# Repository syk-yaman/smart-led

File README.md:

# Smart LED

An AVR board to control home lighting autonomously. It provides automatic control of LED lighting (12vdc) according to:

* Time schedule: active during daily work time except for holidays.
* People movement: turning on lighting automatically when sensing movement using a PIR extension.
* Electric supply status: provides auxiliary lighting when needed (in case of a power outage).
* Illumination level sensing: no need to turn on the lighting when there is enough lighting.

Also providing manual control:

- Directly using onboard buttons.
- Remotely using an infrared remote control (RC5 based).

# Specifications

**Inputs:**

- 12v DC power supply.
- 220v AC (power detection).

**Output:**

- 12v DC power supply for LEDs.

**Schematic**:

**Main parts:**

- ATmega 8A
- DS1307 RTC
- PIR module ([link](https://www.adafruit.com/product/189))
- 5v DC Relay
- Infrared receiver

See [BOM](https://raw.githubusercontent.com/syk-yaman/smart-led/master/PCB/BOM.txt) for further details.

# Development

Required tools:

* Atmel Studio
* Autodesk Eagle
* A brain

**BE AWARE OF ELECTRIC SHOCK, 220V POWER SUPPLY SHOULD BE TAKEN SERIOUSLY. PLEASE TAKE SAFETY MEASURES FIRST**

## License

###### The software side is licensed under MIT License

```
MIT License

Copyright (c) [year] [fullname]

Permission is hereby granted, free of charge, to any person obtaining a copy
of this software and associated documentation files (the "Software"), to deal
in the Software without restriction, including without limitation the rights
to use, copy, modify, merge, publish, distribute, sublicense, and/or sell
copies of the Software, and to permit persons to whom the Software is
furnished to do so, subject to the following conditions:

The above copyright notice and this permission notice shall be included in all
copies or substantial portions of the Software.

THE SOFTWARE IS PROVIDED "AS IS", WITHOUT WARRANTY OF ANY KIND, EXPRESS OR
IMPLIED, INCLUDING BUT NOT LIMITED TO THE WARRANTIES OF MERCHANTABILITY,
FITNESS FOR A PARTICULAR PURPOSE AND NONINFRINGEMENT. IN NO EVENT SHALL THE
AUTHORS OR COPYRIGHT HOLDERS BE LIABLE FOR ANY CLAIM, DAMAGES OR OTHER
LIABILITY, WHETHER IN AN ACTION OF CONTRACT, TORT OR OTHERWISE, ARISING FROM,
OUT OF OR IN CONNECTION WITH THE SOFTWARE OR THE USE OR OTHER DEALINGS IN THE
SOFTWARE.
```

###### The hardware side is licensed under CERN License

```
This documentation describes Open Hardware and is licensed under the CERN OHL v. 1.2.

You may redistribute and modify this documentation under the terms of the CERN OHL v.1.2. (http://ohwr.org/cernohl). This documentation is distributed WITHOUT ANY EXPRESS OR IMPLIED WARRANTY, INCLUDING OF MERCHANTABILITY, SATISFACTORY QUALITY AND FITNESS FOR A PARTICULAR PURPOSE. Please see the CERN OHL v.1.2 for applicable conditions
```

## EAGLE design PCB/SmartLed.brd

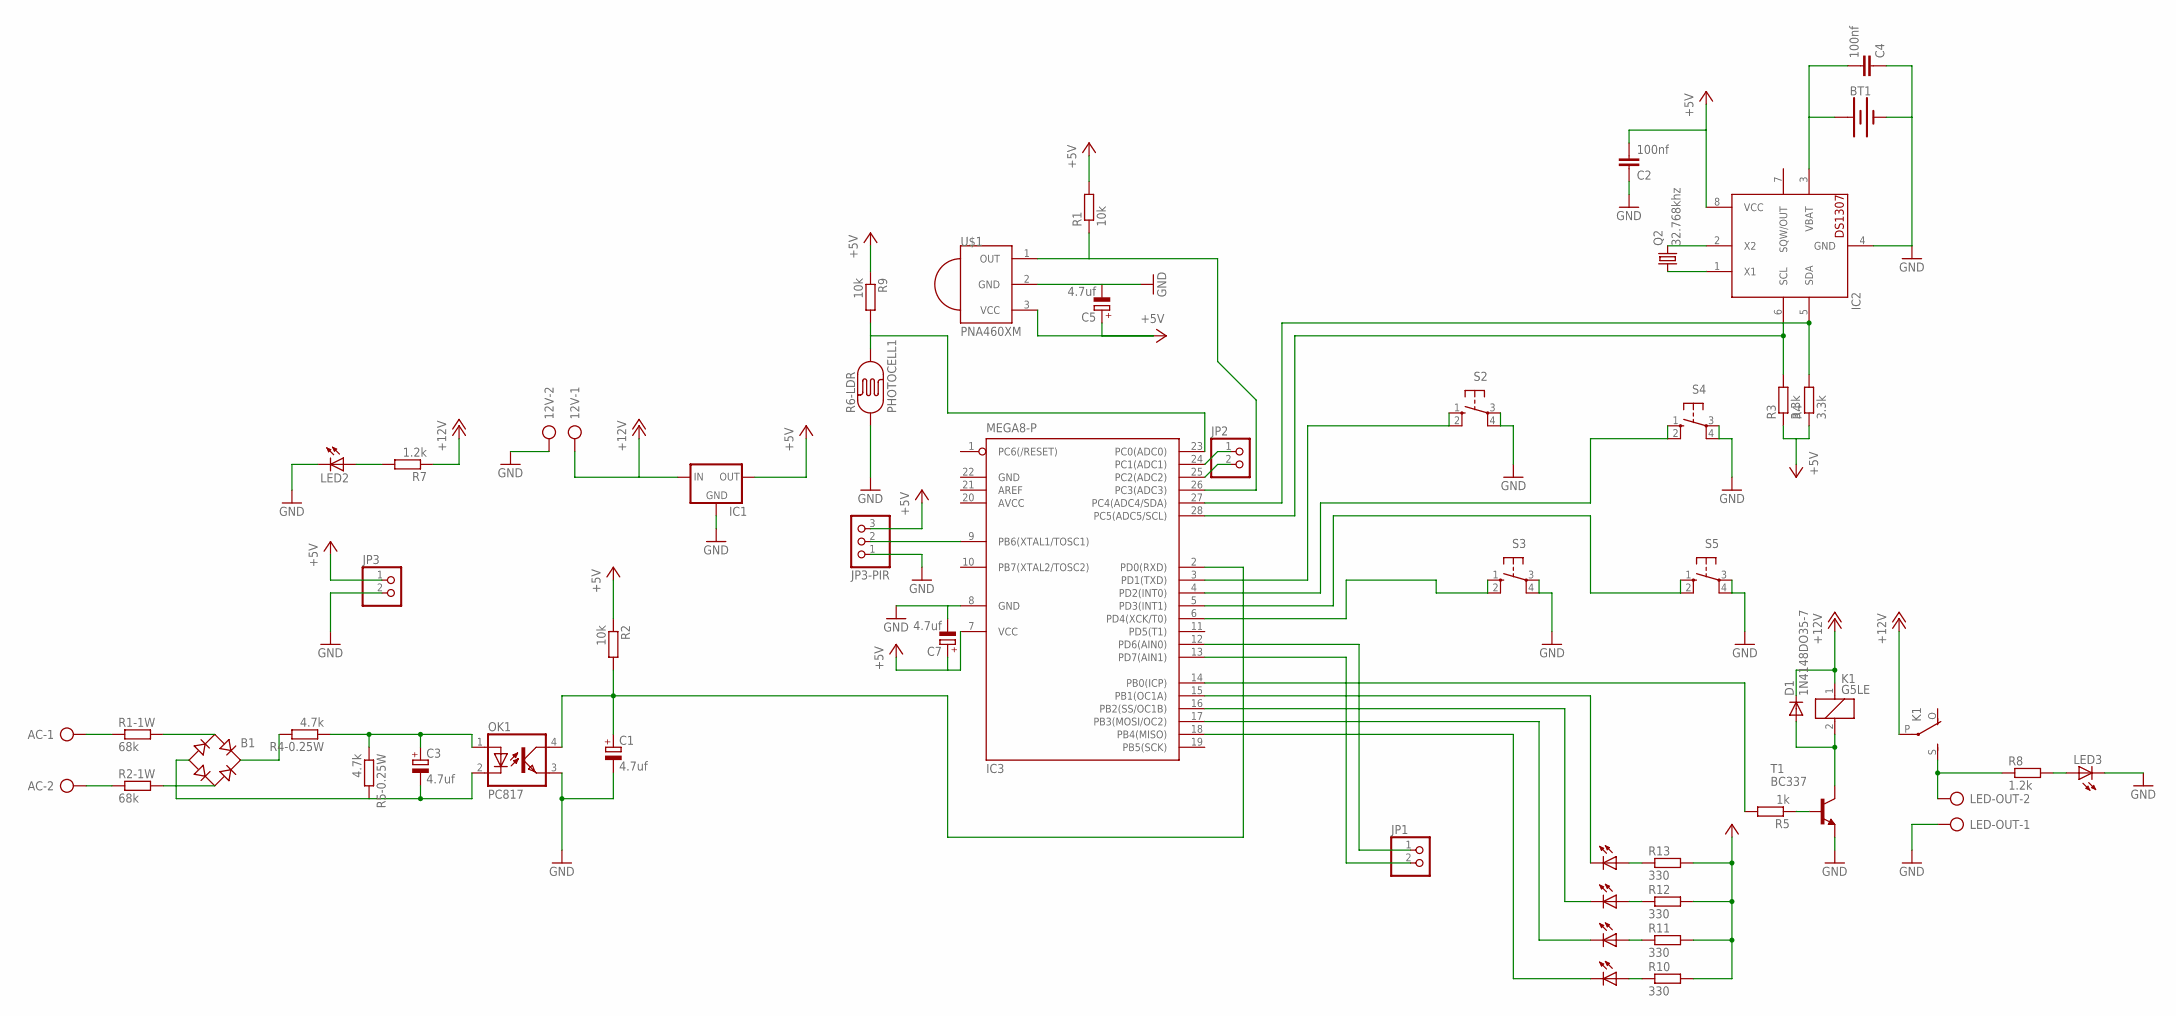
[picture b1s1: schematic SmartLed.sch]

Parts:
12V: AK500/2
AC: AK500/2
B1: RB1A
BT1: BATTERY-20MM_PTH; BATTCOM_20MM_PTH
C1, C3, C5, C7: 4.7uf; E2,5-5
C2, C4: 100nf; C025-025X050
D1: 1N4148DO35-7; DO35-7
IC1: 78XXL
IC2: DS1307; DIL08
IC3: MEGA8-P; DIL28-3
JP1, JP2, JP3: PINHD-1X2; 1X02
JP3-PIR: PINHD-1X3; 1X03
K1: G5LE
LED2, LED3, LED5, LED6, LED7, LED8: LED3MM
LED-OUT: AK500/2
OK1: PC817; DIL04
Q2: 32.768khz; TC26V
R1, R2, R9: 10k; 0207/10
R1-1W, R2-1W: 68k; 0411/15
R3, R4: 3.3k; 0207/10
R4-0.25W, R5-0.25W: 4.7k; 0207/10
R5: 1k; 0207/10
R6-LDR: PHOTOCELL1; LDR_OFFBOARD
R7, R8: 1.2k; 0207/10
R10, R11, R12, R13: 330; 0207/10
S2, S3, S4, S5: 10-XX; B3F-10XX
T1: BC337; TO92
U$1: PNA460XM

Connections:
+5V: C2.2, C5.+, C7.+, IC1.OUT, IC2.8 (VCC), IC3.7 (VCC), JP3.1, JP3-PIR.3, R1.2, R2.1, R3.1, R4.1, R9.1, R10.2, R11.2, R12.2, R13.2, U$1.3 (VCC)
+12V: 12V.1, D1.C, IC1.IN, K1.1, K1.P, R7.1
AVCC: IC3.20 (AVCC)
GND: 12V.2, BT1.2 (-), C1.-, C2.1, C4.1, C5.-, C7.-, IC1.GND, IC2.4 (GND), IC3.8 (GND), IC3.22 (GND), JP3.2, JP3-PIR.1, LED2.K (C), LED3.K (C), LED-OUT.1, OK1.3 (EMIT), R6-LDR.1, S2.3, S2.4 (P1), S3.3, S3.4 (P1), S4.3, S4.4 (P1), S5.3, S5.4 (P1), T1.1 (E), U$1.2 (GND)
unnamed: AC.1, R1-1W.1
unnamed: AC.2, R2-1W.1
unnamed: B1.AC1, R1-1W.2
unnamed: B1.AC2, R2-1W.2
unnamed: B1.+, R4-0.25W.2
unnamed: C3.+, OK1.1 (A), R4-0.25W.1, R5-0.25W.1
unnamed: B1.-, C3.-, OK1.2 (C), R5-0.25W.2
unnamed: K1.S, LED-OUT.2, R8.1
unnamed: R5.1, T1.2 (B)
unnamed: IC3.14 (PB0(ICP)), R5.2
unnamed: C1.+, IC3.2 (PD0(RXD)), OK1.4 (COL), R2.2
unnamed: IC2.6 (SCL), IC3.28 (PC5(ADC5/SCL)), R3.2
unnamed: IC2.5 (SDA), IC3.27 (PC4(ADC4/SDA)), R4.2
unnamed: D1.A, K1.2, T1.3 (C)
unnamed: LED2.A, R7.2
unnamed: LED3.A, R8.2
unnamed: IC3.15 (PB1(OC1A)), LED8.K (C)
unnamed: LED8.A, R13.1
unnamed: IC3.9 (PB6(XTAL1/TOSC1)), JP3-PIR.2
unnamed: IC3.16 (PB2(SS/OC1B)), LED7.K (C)
unnamed: IC2.1 (X1), Q2.1
unnamed: IC2.2 (X2), Q2.2
unnamed: LED7.A, R12.1
unnamed: IC3.17 (PB3(MOSI/OC2)), LED6.K (C)
unnamed: LED6.A, R11.1
unnamed: IC3.18 (PB4(MISO)), LED5.K (C)
unnamed: LED5.A, R10.1
unnamed: IC3.3 (PD1(TXD)), S2.1 (S), S2.2 (S1)
unnamed: IC3.24 (PC1(ADC1)), JP2.1
unnamed: IC3.6 (PD4(XCK/T0)), S3.1 (S), S3.2 (S1)
unnamed: IC3.4 (PD2(INT0)), S4.1 (S), S4.2 (S1)
unnamed: IC3.5 (PD3(INT1)), S5.1 (S), S5.2 (S1)
unnamed: IC3.25 (PC2(ADC2)), JP2.2
unnamed: IC3.23 (PC0(ADC0)), R6-LDR.2, R9.2
unnamed: IC3.12 (PD6(AIN0)), JP1.1
unnamed: IC3.13 (PD7(AIN1)), JP1.2
unnamed: BT1.1 (+), C4.2, IC2.3 (VBAT)
unnamed: IC3.26 (PC3(ADC3)), R1.1, U$1.1 (OUT)

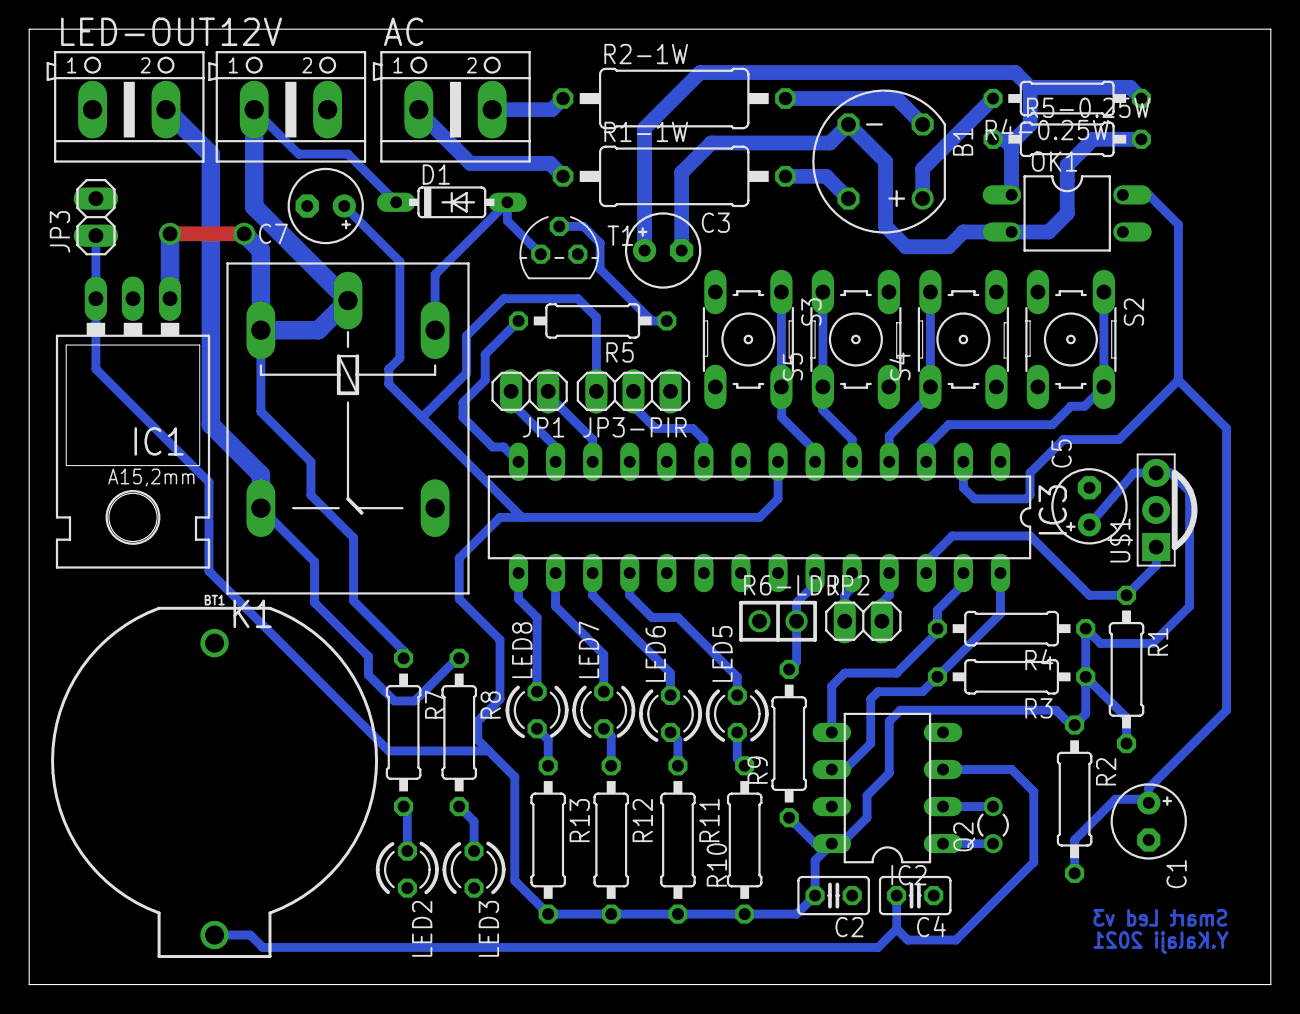
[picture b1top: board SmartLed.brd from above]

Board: 2 copper layers, 85.1 x 65.5 mm, 51 parts (0 on the bottom side), 41 nets.

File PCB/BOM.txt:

Partlist exported from C:/Users/Yaman-PC/projects/smart-led/PCB/SmartLed.sch at 12-Jun-18 10:46 PM

Qty Value        Device           Package          Parts                              Description                          MF MPN          OC_FARNELL OC_NEWARK PROD_ID    SF_SKU   
4                10-XX            B3F-10XX         S2, S3, S4, S5                     OMRON SWITCH                            B3F-1000     176432     36M3542                       
1                79XXL            79XXL            IC1                                VOLTAGE REGULATOR                                                                             
3                AK500/2          AK500/2          12V, AC, LED-OUT                   CONNECTOR                                            unknown    unknown                       
1                BATTERY-20MM_PTH BATTCOM_20MM_PTH BT1                                Battery - Single Cell                                                     BATT-09031 PRT-00783
6                LED3MM           LED3MM           LED2, LED3, LED5, LED6, LED7, LED8 LED                                                                                           
2                PINHD-1X2        1X02             JP1, JP3                           PIN HEADER                                                                                    
1                PINHD-1X3        1X03             JP3-PIR                            PIN HEADER                                                                                    
1                PINHD-1X4        1X04             JP2                                PIN HEADER                                                                                    
1                RB1A             RB1A             B1                                 RECTIFIER                                                                                     
2   1.2k         R-EU_0207/10     0207/10          R7, R8                             RESISTOR, European symbol                                                                     
2   100nf        C-EU025-025X050  C025-025X050     C2, C4                             CAPACITOR, European symbol                                                                    
2   10k          R-EU_0207/10     0207/10          R1, R2                             RESISTOR, European symbol                                                                     
1   1N4148DO35-7 1N4148DO35-7     DO35-7           D1                                 DIODE                                                                                         
1   1k           R-EU_0207/10     0207/10          R5                                 RESISTOR, European symbol                                                                     
2   3.3k         R-EU_0207/10     0207/10          R3, R4                             RESISTOR, European symbol                                                                     
1   32.768khz    CRYSTALTC26V     TC26V            Q2                                 CRYSTAL                                              unknown    unknown                       
4   330          R-EU_0207/10     0207/10          R10, R11, R12, R13                 RESISTOR, European symbol                                                                     
2   4.7k         R-EU_0207/10     0207/10          R4-0.25W, R5-0.25W                 RESISTOR, European symbol                                                                     
4   4.7uf        CPOL-EUE2.5-5    E2,5-5           C1, C3, C5, C7                     POLARIZED CAPACITOR, European symbol                                                          
2   68k          R-EU_0411/15     0411/15          R1-1W, R2-1W                       RESISTOR, European symbol                                                                     
1   BC337        BC337            TO92             T1                                 NPN TRANSISTOR                                                                                
1   DS1307       DS1307           DIL08            IC2                                DS1307                                                                                        
1   G5LE         G5LE             G5LE             K1                                 RELAY                                                unknown    unknown                       
1   MEGA8-P      MEGA8-P          DIL28-3          IC3                                MICROCONTROLLER                                      unknown    unknown                       
1   PC817        PC817            DIL04            OK1                                SHARP OPTO COUPLER                      PC817X4J000F 9707727    97K7059                       
1   PNA460XM     PNA460XM         PNA460XM         U$1                                IR 38KHz receiver

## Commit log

2018-04-24 Add used libraries in Eagle
2018-04-24 Add 100n capacitor beside 3.6v lithium battery & change the battery footprint
2018-04-24 Move library folder inside PCB folder
2018-04-24 Remove unused comments
2018-04-25 Fix a small bug in current active time method
2018-04-25 Update Proteus file to new hex location
2018-05-01 Add watchdog timer
2018-05-13 Change turn off time to 7 PM instead of 6 PM
2018-06-08 Infrared receiver was added & crystal footprint size was corrected
2018-06-08 Refactor PCB design (several enhancements)
2018-06-09 Add PIR sensor pins to PCB
2018-06-11 Add a pinhead for light sensor
2018-06-12 Add Bill of materials
2018-06-12 Add PCB & Schematic images
2018-06-16 Fix wrong voltage regulator footprint
2018-06-16 Added an LDR library
2018-06-16 Add a LDR off-board sensor
2020-08-15 Working on adding battery voltage meter & adding esp8266 connections header
2020-08-15 Add a library for 3.3v voltage regulator
2021-09-04 Fix leds draining power from MCU I/O pins & make 12v lines thicker (after some problems caused by long time usge)
2021-09-07 Change leds logic (now activated on low)
2021-09-09 Add an RC5 library (from https://github.com/pinkeen/avr-rc5)
2021-09-10 Implemented features: LDR with PIR sensor & infrared receiver (now SmartLed can be controller via remote control instead of pressing buttons)
2021-09-10 Removed the RC5 protocol files, we need to upgrade the PCB in order to use them
2021-09-10 Updated the BOM
2021-09-10 Increased the LDR threshold
2021-09-10 Added the V3 hex file
2021-09-10 Update schematic & PCB pictures
2021-09-10 Add some pics
2021-09-10 Add cover photo
2021-09-10 Finally, adding a README.md file, what a relief
2021-09-10 Fixed some typos & updated the licenses

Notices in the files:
parts and their libraries:
SparkFun-Batteries: Licensing: Creative Commons ShareAlike 4.0 International - https://creativecommons.org/licenses/by-sa/4.0
